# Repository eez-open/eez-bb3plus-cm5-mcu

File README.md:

### This is a WORK IN PROGRESS!

---

### Ownership and License
The contributors are listed in CONTRIB.TXT. 

Licenses | OSHWA UID
--|--
 | 

### Overview

The MCU module uses a high performance STM32 MCU and is pin compatible with Raspberry Pi CM5. The MCU cannot generate an HDMI compatible signal, so a [TI TFP410](https://www.ti.com/product/TFP410) is used to convert 24-bit RGB to HDMI compatible signal. Since the BB3+ offers dual display: a built-in 5" TFT touchscreen and an external monitor, a 1:2 high speed mux ([TS3DV642](https://www.ti.com/product/TS3DV642)) is used for destination selection.

### Feature list

* [Raspberry Pi CM5](https://www.raspberrypi.com/products/compute-module-5) form factor (55 x 45 mm)
* [STM32H7R7L8H6H](https://www.st.com/en/microcontrollers-microprocessors/stm32h7r7l8.html) 32-bit High-Performance Arm Cortex-M7 MCU, 600 MHz, NeoChrom GPU
* 32 MB PSRAM
* 32 MB Flash memory
* Micro SD Card socket
* Two USB ports (1x FS with [1:2 Mux](https://www.diodes.com/part/view/PI3USB102), 1x FS/HS)
* 10/100 Mbps Ethernet
* 24-bit color video output with 1:2 MUX (HDMI® compatible)
* 6-layer PCB (without buried/blind vias)

### Related topics and links

* Intergalaktik [BB3-CM4](https://intergalaktik.eu/projects/bb3-cm4)
* [EEZ BB3+](https://github.com/eez-open/eez-bb3plus)
* [DIB DCP405+](https://github.com/eez-open/dib-dcp405plus) power module
* [EEZ BB3](https://github.com/eez-open/modular-psu)
* [EEZ Studio](https://www.envox.eu/studio/studio-introduction)
* [Discord](https://discord.com/invite/q5KAeeenNG) server
* [X](https://x.com/envox) (ex Twitter)
* [YouTube](https://www.youtube.com/c/eezopen) channel
* [EEVblog forum](https://www.eevblog.com/forum/projects/eez-h25005-a-possible-successor-of-eez-h24005-programmable-power-supply/) discussion

---

This work is financed by [NLnet](https://nlnet.nl/project/BB3-CM5/) foundation

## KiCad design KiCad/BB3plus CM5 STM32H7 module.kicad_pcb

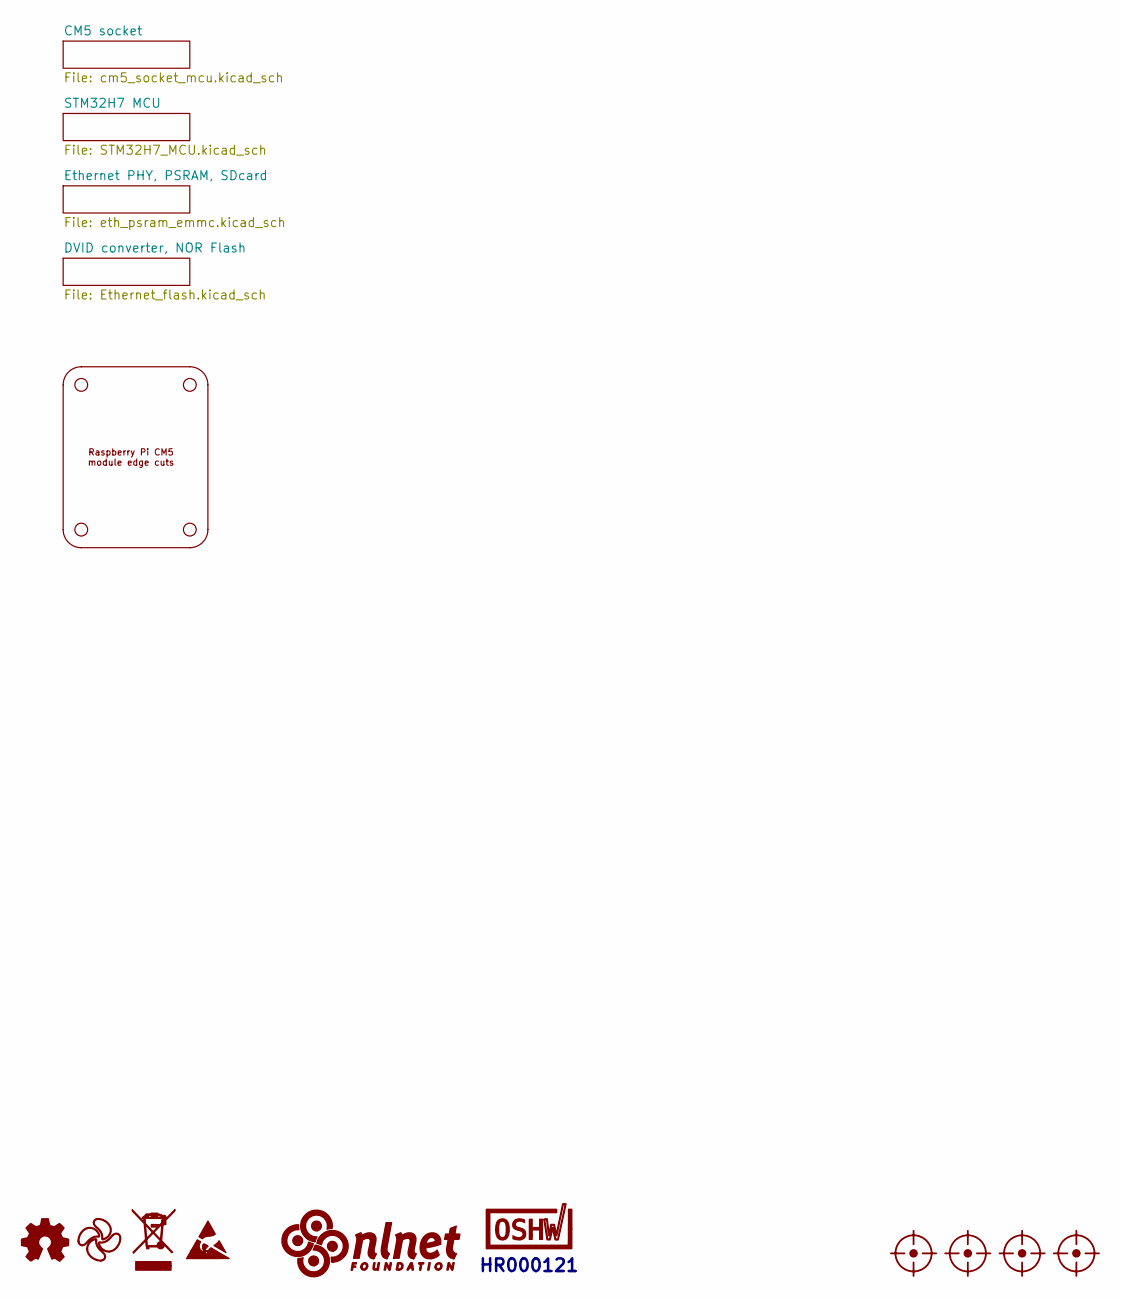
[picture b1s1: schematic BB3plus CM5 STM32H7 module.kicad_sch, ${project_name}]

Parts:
FM1, FM2, FM3, FM4: Fiducial_0.75mm_Mask1.5mm
LOGO1: Open HW logo; Open HW logo (5.7x6mm)
LOGO2: EEZ logo; EEZ logo (outline 6mm)
LOGO3: WEEE logo
LOGO4: ESD logo
LOGO5: NLnet logo
LOGO6: OSHWA logo; OSHWA logo 6.6mm
Module1: Raspberry-Pi-CM5 (SoM)_EdgeCuts

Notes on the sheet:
HR000121

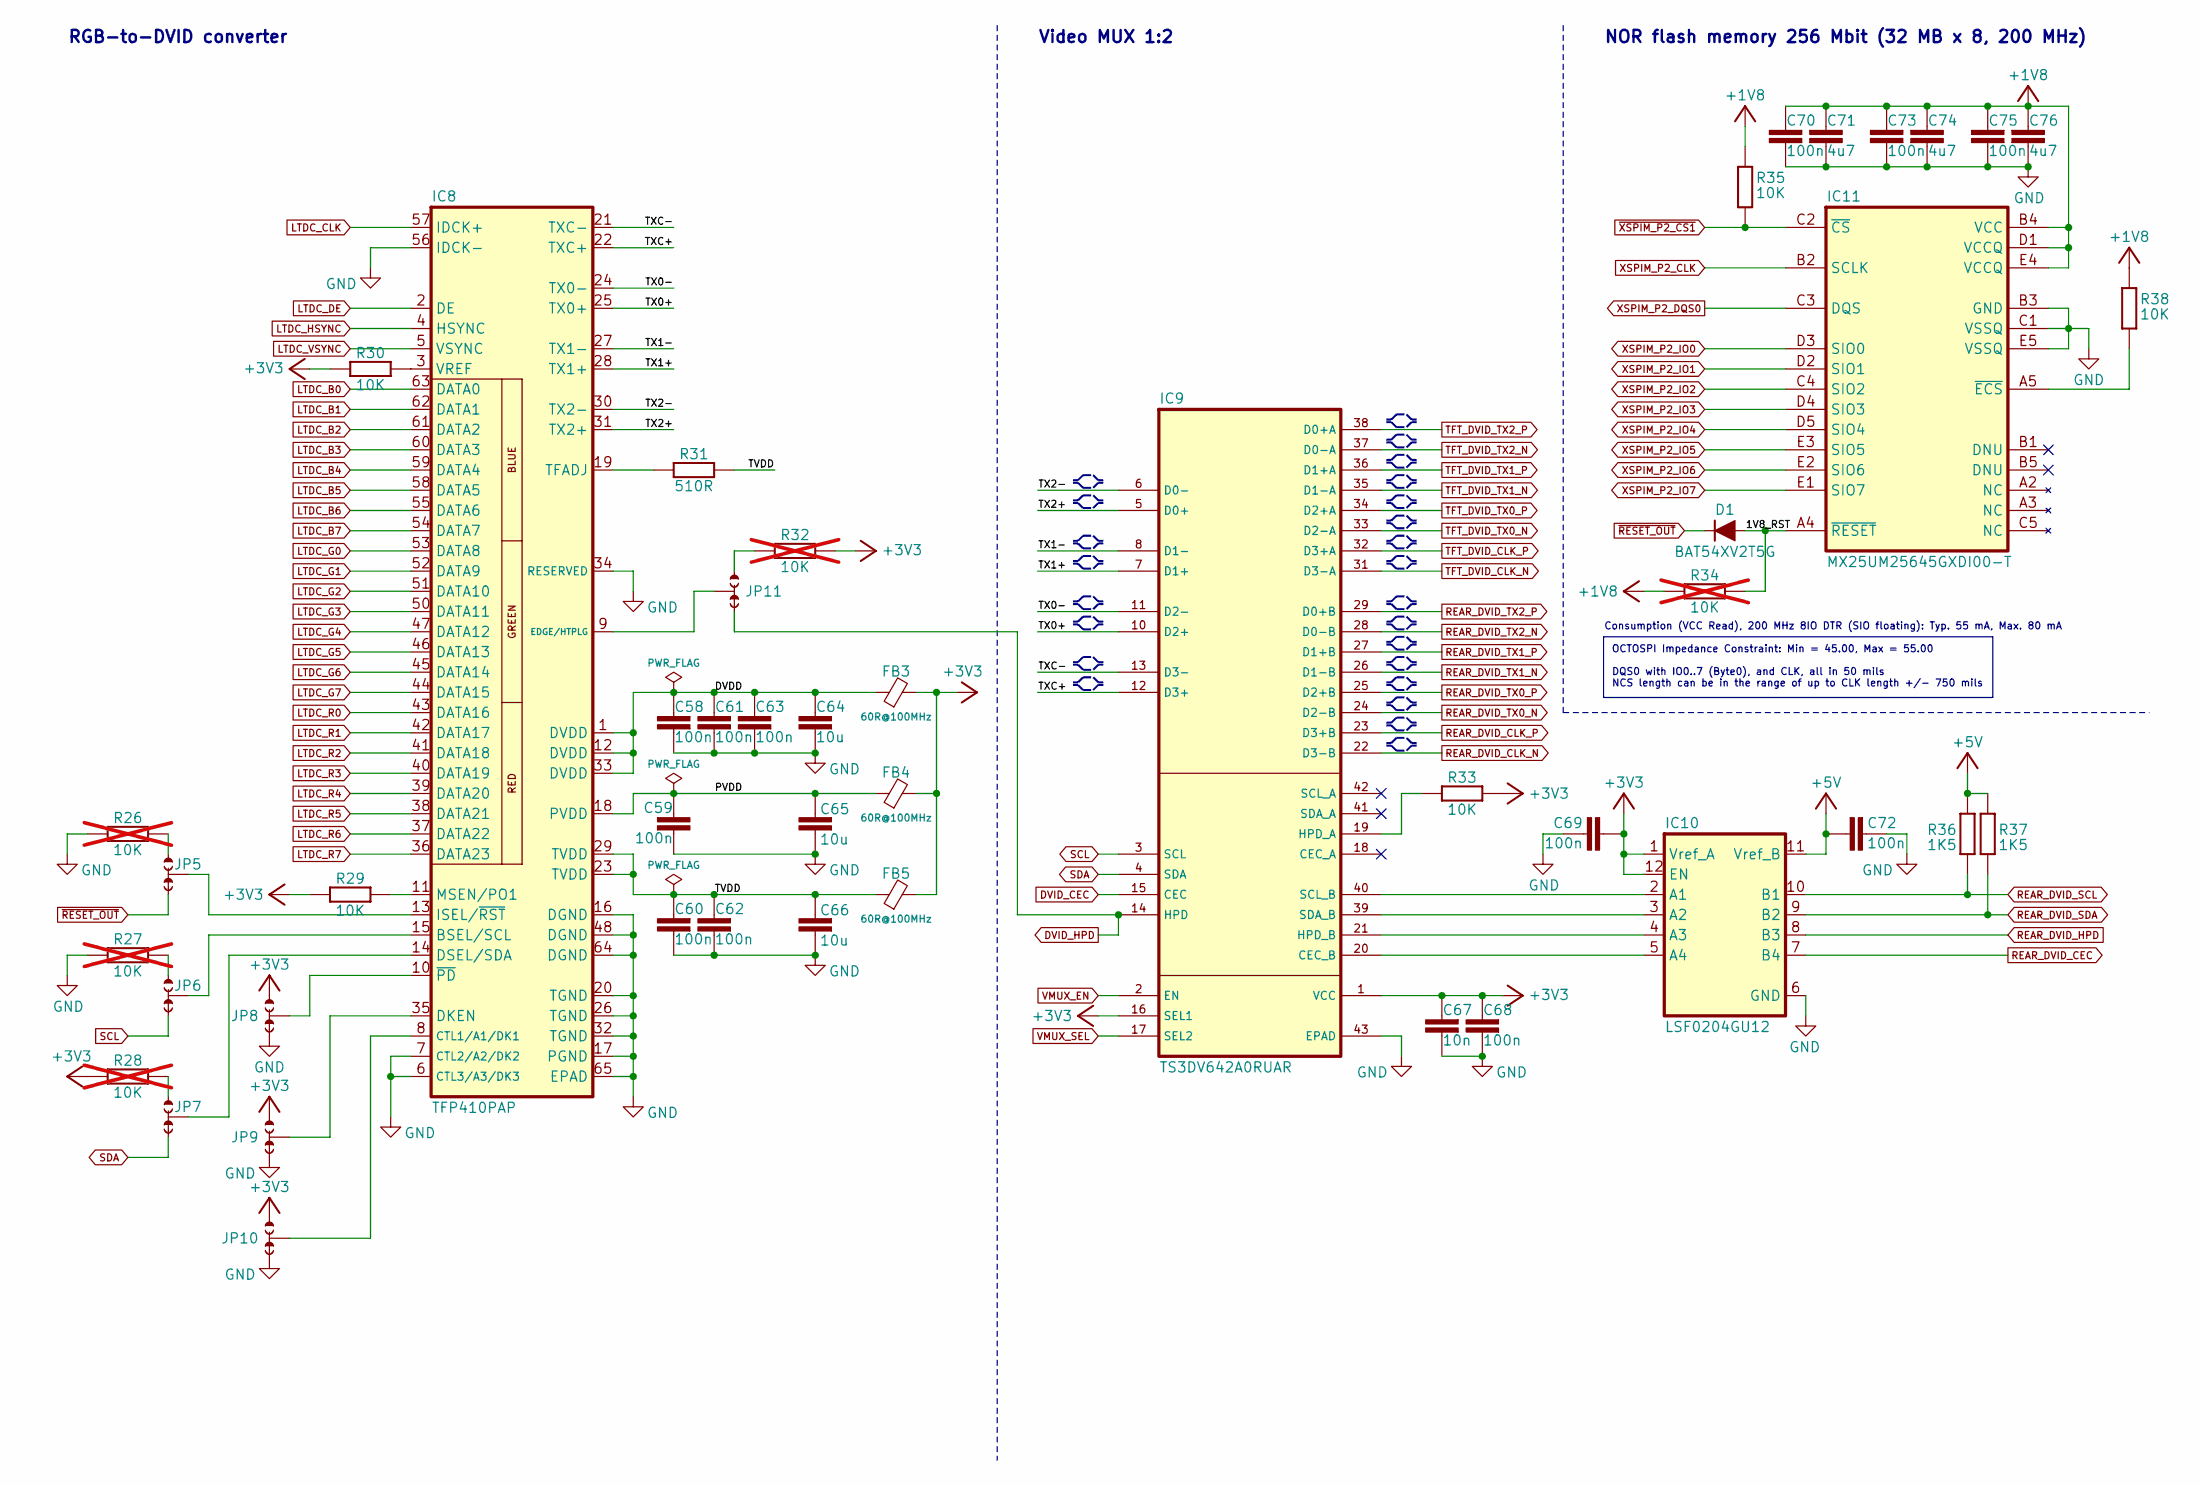
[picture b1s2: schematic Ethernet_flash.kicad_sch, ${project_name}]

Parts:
C58, C59, C60, C61, C62, C63, C68, C69, C70, C72, C73, C75: 100n; C_0402_1005Metric; DigiKey 490-6287-1-ND
C64, C65, C66: 10u; C_0603_1608Metric; DigiKey 1276-1052-6-ND
C67: 10n; C_0402_1005Metric; DigiKey 490-6309-1-ND
C71, C74, C76: 4u7; C_0603_1608Metric; DigiKey 1276-1044-1-ND
D1: BAT54XV2T5G; SOD-523F_0P9X1P3_ONS; DigiKey BAT54XV2T5GOSCT-ND
FB3, FB4, FB5: 60R@100MHz; BEAD0603; DigiKey 490-7809-1-ND
IC8: TFP410PAP; PAP64_5X5-L; DigiKey 296-12666-ND
IC9: TS3DV642A0RUAR; RUA42_7P55X2P05; DigiKey 296-39510-1-ND
IC10: LSF0204GU12; XQFN12_SOT1174-1_NEX-L; DigiKey 1727-LSF0204GU12-Q100XTR-ND
IC11: MX25UM25645GXDI00-T; APS256XXN-OBR-BG_APY-L; DigiKey 1092-MX25UM25645GXDI00-ND
JP5, JP6, JP7, JP8, JP9, JP10, JP11: JP3 shorted (0603)
R26, R27, R28, R32, R34: 10K; R_0402_1005Metric; DigiKey 311-10.0KLRCT-ND; not fitted
R29, R30, R33, R35, R38: 10K; R_0402_1005Metric; DigiKey 311-10.0KLRCT-ND
R31: 510R; R_0402_1005Metric; DigiKey 13-RC0402FR-13510RLCT-ND
R36, R37: 1K5; R_0402_1005Metric; DigiKey 311-1.50KLRCT-ND

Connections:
+1V8: C70.1, C71.1, C73.1, C74.1, C75.1, C76.1, IC11.B4 (VCC), IC11.D1 (VCCQ), IC11.E4 (VCCQ), R34.2, R35.2, R38.2; also elsewhere on the board
+3V3: C67.1, C68.1, C69.2, FB3.2, FB4.2, FB5.2, IC9.1 (VCC), IC9.16 (SEL1), IC10.1 (Vref_A), IC10.12 (EN), JP8.NO, JP9.NO, JP10.NO, R28.2, R29.1, R30.2, R32.2, R33.2; also elsewhere on the board
+5V: C72.2, IC10.11 (Vref_B), R36.2, R37.2; also elsewhere on the board
/DVID converter, NOR Flash/1V8_RST: D1.A, IC11.A4 (~RESET), R34.1
/DVID converter, NOR Flash/DVDD: C58.1, C61.1, C63.1, C64.1, FB3.1, IC8.1 (DVDD), IC8.12 (DVDD), IC8.33 (DVDD)
/DVID converter, NOR Flash/PVDD: C59.1, C65.2, FB4.1, IC8.18 (PVDD)
/DVID converter, NOR Flash/TVDD: C60.1, C62.1, C66.2, FB5.1, IC8.23 (TVDD), IC8.29 (TVDD), R31.2
/DVID converter, NOR Flash/TX0+: IC8.25 (TX0+), IC9.10 (D2+)
/DVID converter, NOR Flash/TX0-: IC8.24 (TX0-), IC9.11 (D2-)
/DVID converter, NOR Flash/TX1+: IC8.28 (TX1+), IC9.7 (D1+)
/DVID converter, NOR Flash/TX1-: IC8.27 (TX1-), IC9.8 (D1-)
/DVID converter, NOR Flash/TX2+: IC8.31 (TX2+), IC9.5 (D0+)
/DVID converter, NOR Flash/TX2-: IC8.30 (TX2-), IC9.6 (D0-)
/DVID converter, NOR Flash/TXC+: IC8.22 (TXC+), IC9.12 (D3+)
/DVID converter, NOR Flash/TXC-: IC8.21 (TXC-), IC9.13 (D3-)
DVID_CEC: IC9.15 (CEC); also elsewhere on the board
DVID_HPD: IC9.14 (HPD), JP11.NC; also elsewhere on the board
GND: C58.2, C59.2, C60.2, C61.2, C62.2, C63.2, C64.2, C65.1, C66.1, C67.2, C68.2, C69.1, C70.2, C71.2, C72.1, C73.2, C74.2, C75.2, C76.2, IC8.6 (CTL3/A3/DK3), IC8.7 (CTL2/A2/DK2), IC8.16 (DGND), IC8.17 (PGND), IC8.20 (TGND), IC8.26 (TGND), IC8.32 (TGND), IC8.34 (RESERVED), IC8.48 (DGND), IC8.56 (IDCK-), IC8.64 (DGND), IC8.65 (EPAD), IC9.43 (EPAD), IC10.6 (GND), IC11.B3 (GND), IC11.C1 (VSSQ), IC11.E5 (VSSQ), JP8.NC, JP9.NC, JP10.NC, R26.2, R27.2; also elsewhere on the board
LTDC_B0: IC8.63 (DATA0); also elsewhere on the board
LTDC_B1: IC8.62 (DATA1); also elsewhere on the board
LTDC_B2: IC8.61 (DATA2); also elsewhere on the board
LTDC_B3: IC8.60 (DATA3); also elsewhere on the board
LTDC_B4: IC8.59 (DATA4); also elsewhere on the board
LTDC_B5: IC8.58 (DATA5); also elsewhere on the board
LTDC_B6: IC8.55 (DATA6); also elsewhere on the board
LTDC_B7: IC8.54 (DATA7); also elsewhere on the board
LTDC_CLK: IC8.57 (IDCK+); also elsewhere on the board
LTDC_DE: IC8.2 (DE); also elsewhere on the board
LTDC_G0: IC8.53 (DATA8); also elsewhere on the board
LTDC_G1: IC8.52 (DATA9); also elsewhere on the board
LTDC_G2: IC8.51 (DATA10); also elsewhere on the board
LTDC_G3: IC8.50 (DATA11); also elsewhere on the board
LTDC_G4: IC8.47 (DATA12); also elsewhere on the board
LTDC_G5: IC8.46 (DATA13); also elsewhere on the board
LTDC_G6: IC8.45 (DATA14); also elsewhere on the board
LTDC_G7: IC8.44 (DATA15); also elsewhere on the board
LTDC_HSYNC: IC8.4 (HSYNC); also elsewhere on the board
LTDC_R0: IC8.43 (DATA16); also elsewhere on the board
LTDC_R1: IC8.42 (DATA17); also elsewhere on the board
LTDC_R2: IC8.41 (DATA18); also elsewhere on the board
LTDC_R3: IC8.40 (DATA19); also elsewhere on the board
LTDC_R4: IC8.39 (DATA20); also elsewhere on the board
LTDC_R5: IC8.38 (DATA21); also elsewhere on the board
LTDC_R6: IC8.37 (DATA22); also elsewhere on the board
LTDC_R7: IC8.36 (DATA23); also elsewhere on the board
LTDC_VSYNC: IC8.5 (VSYNC); also elsewhere on the board
unnamed: IC8.15 (BSEL/SCL), JP6.COM
unnamed: IC8.8 (CTL1/A1/DK1), JP10.COM
unnamed: IC8.35 (DKEN), JP9.COM
unnamed: IC8.14 (DSEL/SDA), JP7.COM
unnamed: IC8.9 (EDGE/HTPLG), JP11.COM
unnamed: IC8.13 (ISEL/~RST), JP5.COM
unnamed: IC8.11 (MSEN/PO1), R29.2
unnamed: IC8.19 (TFADJ), R31.1
unnamed: IC8.3 (VREF), R30.1
unnamed: IC8.10 (~PD), JP8.COM
unnamed: IC9.19 (HPD_A), R33.1
unnamed: IC9.40 (SCL_B), IC10.2 (A1)
unnamed: IC9.39 (SDA_B), IC10.3 (A2)
unnamed: IC9.21 (HPD_B), IC10.4 (A3)
unnamed: IC9.20 (CEC_B), IC10.5 (A4)
unnamed: IC11.A5 (~ECS), R38.1
unnamed: JP5.NO, R26.1
unnamed: JP6.NO, R27.1
unnamed: JP7.NO, R28.1
unnamed: JP11.NO, R32.1
REAR_DVID_CEC: IC10.7 (B4); also elsewhere on the board
REAR_DVID_CLK_N: IC9.22 (D3-B); also elsewhere on the board
REAR_DVID_CLK_P: IC9.23 (D3+B); also elsewhere on the board
REAR_DVID_HPD: IC10.8 (B3); also elsewhere on the board
REAR_DVID_SCL: IC10.10 (B1), R36.1; also elsewhere on the board
REAR_DVID_SDA: IC10.9 (B2), R37.1; also elsewhere on the board
REAR_DVID_TX0_N: IC9.24 (D2-B); also elsewhere on the board
REAR_DVID_TX0_P: IC9.25 (D2+B); also elsewhere on the board
REAR_DVID_TX1_N: IC9.26 (D1-B); also elsewhere on the board
REAR_DVID_TX1_P: IC9.27 (D1+B); also elsewhere on the board
REAR_DVID_TX2_N: IC9.28 (D0-B); also elsewhere on the board
REAR_DVID_TX2_P: IC9.29 (D0+B); also elsewhere on the board
SCL: IC9.3 (SCL), JP6.NC; also elsewhere on the board
SDA: IC9.4 (SDA), JP7.NC; also elsewhere on the board
TFT_DVID_CLK_N: IC9.31 (D3-A); also elsewhere on the board
TFT_DVID_CLK_P: IC9.32 (D3+A); also elsewhere on the board
TFT_DVID_TX0_N: IC9.33 (D2-A); also elsewhere on the board
TFT_DVID_TX0_P: IC9.34 (D2+A); also elsewhere on the board
TFT_DVID_TX1_N: IC9.35 (D1-A); also elsewhere on the board
TFT_DVID_TX1_P: IC9.36 (D1+A); also elsewhere on the board
TFT_DVID_TX2_N: IC9.37 (D0-A); also elsewhere on the board
TFT_DVID_TX2_P: IC9.38 (D0+A); also elsewhere on the board
VMUX_EN: IC9.2 (EN); also elsewhere on the board
VMUX_SEL: IC9.17 (SEL2); also elsewhere on the board
XSPIM_P2_CLK: IC11.B2 (SCLK); also elsewhere on the board
XSPIM_P2_DQS0: IC11.C3 (DQS); also elsewhere on the board
XSPIM_P2_IO0: IC11.D3 (SIO0); also elsewhere on the board
XSPIM_P2_IO1: IC11.D2 (SIO1); also elsewhere on the board
XSPIM_P2_IO2: IC11.C4 (SIO2); also elsewhere on the board
XSPIM_P2_IO3: IC11.D4 (SIO3); also elsewhere on the board
XSPIM_P2_IO4: IC11.D5 (SIO4); also elsewhere on the board
XSPIM_P2_IO5: IC11.E3 (SIO5); also elsewhere on the board
XSPIM_P2_IO6: IC11.E2 (SIO6); also elsewhere on the board
XSPIM_P2_IO7: IC11.E1 (SIO7); also elsewhere on the board
~RESET_OUT: D1.C, JP5.NC; also elsewhere on the board
~XSPIM_P2_CS1: IC11.C2 (~CS), R35.1; also elsewhere on the board

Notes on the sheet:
RGB-to-DVID converter
Video MUX 1:2
Consumption (VCC Read), 200 MHz 8IO DTR (SIO floating): Typ. 55 mA, Max. 80 mA
NOR flash memory 256 Mbit (32 MB x 8, 200 MHz)
OCTOSPI Impedance Constraint: Min = 45.00, Max = 55.00 DQS0 with IO0..7 (Byte0), and CLK, all in 50 mils NCS length can be in the range of up to CLK length +/- 750 mils

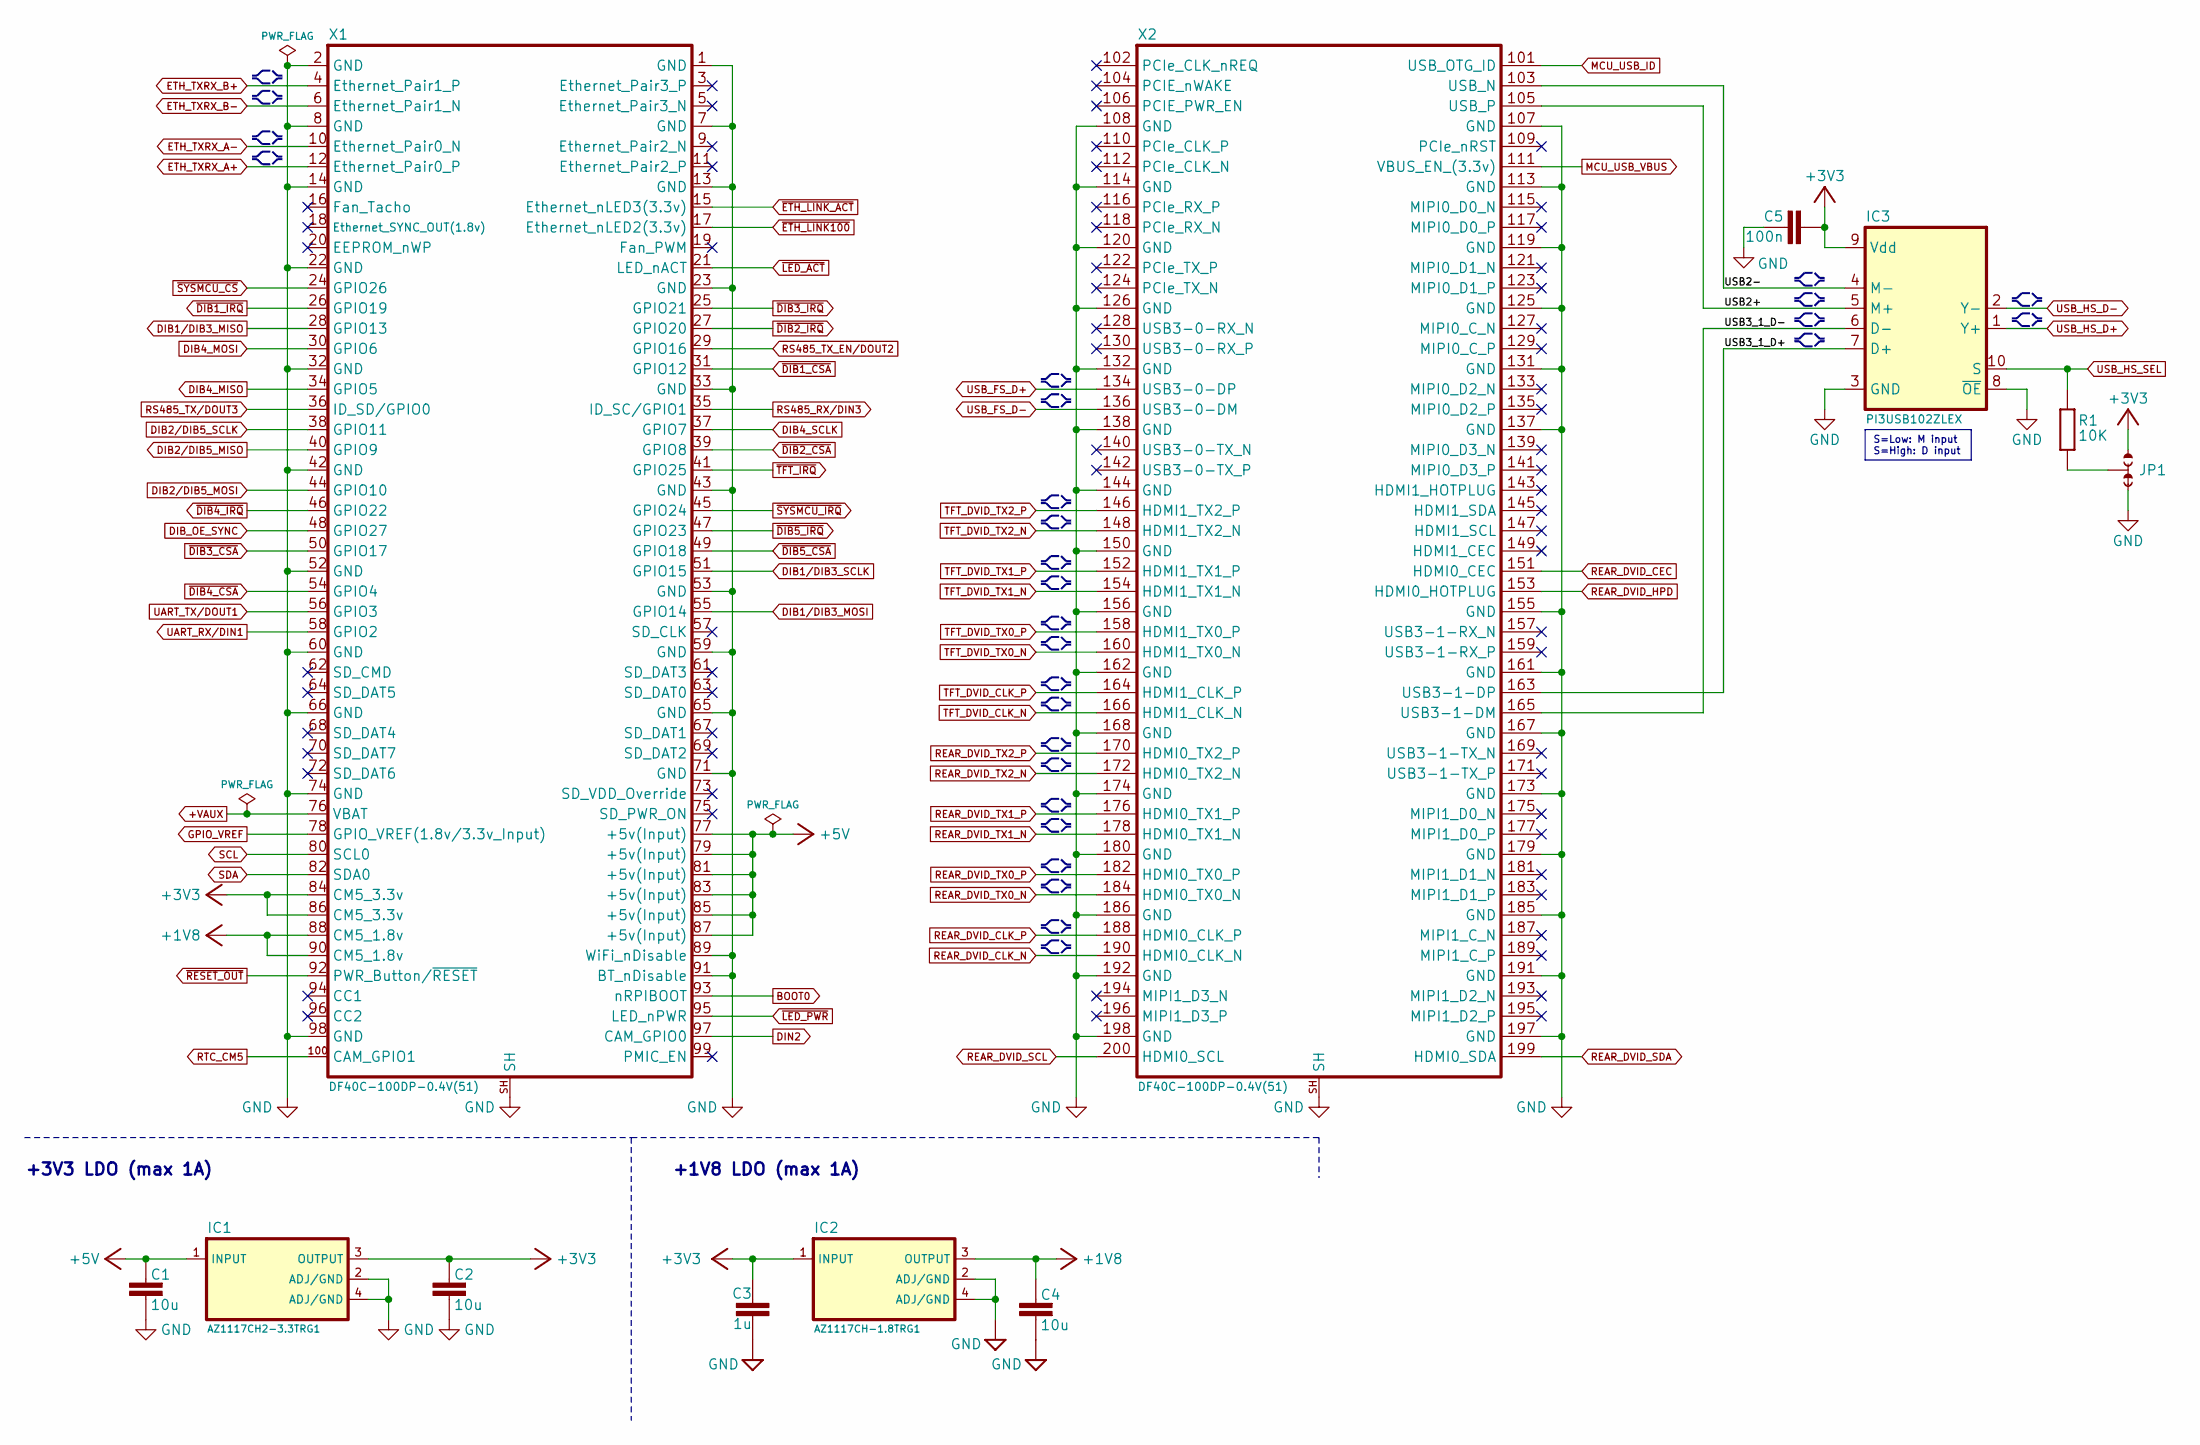
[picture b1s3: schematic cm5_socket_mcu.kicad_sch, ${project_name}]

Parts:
C1, C2, C4: 10u; C_0603_1608Metric; DigiKey 1276-1052-6-ND
C3: 1u; C_0402_1005Metric; DigiKey 490-GRM155C81A105MA12DCT-ND
C5: 100n; C_0402_1005Metric; DigiKey 490-6287-1-ND
IC1: AZ1117CH2-3.3TRG1; SOT223; DigiKey 31-AZ1117CH2-3.3TRG1CT-ND
IC2: AZ1117CH-1.8TRG1; SOT223; DigiKey AZ1117CH-1.8TRG1DICT-ND
IC3: PI3USB102ZLEX; TQFN-10; DigiKey PI3USB102ZLEXCT-ND
JP1: JP3 shorted (0603)
R1: 10K; R_0402_1005Metric; DigiKey 311-10.0KLRCT-ND
X1: DF40C-100DP-0.4V(51); Raspberry-Pi-CM5 (SoM)_Left; DigiKey H11614CT-ND
X2: DF40C-100DP-0.4V(51); Raspberry-Pi-CM5 (SoM)_Right; DigiKey H11614CT-ND

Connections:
+1V8: C4.2, IC2.3 (OUTPUT), X1.88 (CM5_1.8v), X1.90 (CM5_1.8v); also elsewhere on the board
+3V3: C2.2, C3.1, C5.2, IC1.3 (OUTPUT), IC2.1 (INPUT), IC3.9 (Vdd), JP1.NO, X1.84 (CM5_3.3v), X1.86 (CM5_3.3v); also elsewhere on the board
+5V: C1.2, IC1.1 (INPUT), X1.77 (+5v(Input)), X1.79 (+5v(Input)), X1.81 (+5v(Input)), X1.83 (+5v(Input)), X1.85 (+5v(Input)), X1.87 (+5v(Input)); also elsewhere on the board
+VAUX: X1.76 (VBAT); also elsewhere on the board
/CM5 socket/USB2+: IC3.5 (M+), X2.105 (USB_P)
/CM5 socket/USB2-: IC3.4 (M-), X2.103 (USB_N)
/CM5 socket/USB3_1_D+: IC3.7 (D+), X2.163 (USB3-1-DP)
/CM5 socket/USB3_1_D-: IC3.6 (D-), X2.165 (USB3-1-DM)
BOOT0: X1.93 (nRPIBOOT); also elsewhere on the board
DIB1/DIB3_MISO: X1.28 (GPIO13); also elsewhere on the board
DIB1/DIB3_MOSI: X1.55 (GPIO14); also elsewhere on the board
DIB1/DIB3_SCLK: X1.51 (GPIO15); also elsewhere on the board
DIB2/DIB5_MISO: X1.40 (GPIO9); also elsewhere on the board
DIB2/DIB5_MOSI: X1.44 (GPIO10); also elsewhere on the board
DIB2/DIB5_SCLK: X1.38 (GPIO11); also elsewhere on the board
DIB4_MISO: X1.34 (GPIO5); also elsewhere on the board
DIB4_MOSI: X1.30 (GPIO6); also elsewhere on the board
DIB4_SCLK: X1.37 (GPIO7); also elsewhere on the board
DIB_OE_SYNC: X1.48 (GPIO27); also elsewhere on the board
DIN2: X1.97 (CAM_GPIO0); also elsewhere on the board
ETH_TXRX_A+: X1.12 (Ethernet_Pair0_P); also elsewhere on the board
ETH_TXRX_A-: X1.10 (Ethernet_Pair0_N); also elsewhere on the board
ETH_TXRX_B+: X1.4 (Ethernet_Pair1_P); also elsewhere on the board
ETH_TXRX_B-: X1.6 (Ethernet_Pair1_N); also elsewhere on the board
GND: C1.1, C2.1, C3.2, C4.1, C5.1, IC1.2 (ADJ/GND), IC1.4 (ADJ/GND), IC2.2 (ADJ/GND), IC2.4 (ADJ/GND), IC3.3 (GND), IC3.8 (~OE), JP1.NC, X1.1 (GND), X1.2 (GND), X1.7 (GND), X1.8 (GND), X1.13 (GND), X1.14 (GND), X1.22 (GND), X1.23 (GND), X1.32 (GND), X1.33 (GND), X1.42 (GND), X1.43 (GND), X1.52 (GND), X1.53 (GND), X1.59 (GND), X1.60 (GND), X1.65 (GND), X1.66 (GND), X1.71 (GND), X1.74 (GND), X1.89 (WiFi_nDisable), X1.91 (BT_nDisable), X1.98 (GND), X1.SH, X2.107 (GND), X2.108 (GND), X2.113 (GND), X2.114 (GND), X2.119 (GND), X2.120 (GND), X2.125 (GND), X2.126 (GND), X2.131 (GND), X2.132 (GND), X2.137 (GND), X2.138 (GND), X2.144 (GND), X2.150 (GND), X2.155 (GND), X2.156 (GND), X2.161 (GND), X2.162 (GND), X2.167 (GND), X2.168 (GND), X2.173 (GND), X2.174 (GND), X2.179 (GND), X2.180 (GND), X2.185 (GND), X2.186 (GND), X2.191 (GND), X2.192 (GND), X2.197 (GND), X2.198 (GND), X2.SH; also elsewhere on the board
GPIO_VREF: X1.78 (GPIO_VREF(1.8v/3.3v_Input)); also elsewhere on the board
MCU_USB_ID: X2.101 (USB_OTG_ID); also elsewhere on the board
MCU_USB_VBUS: X2.111 (VBUS_EN_(3.3v)); also elsewhere on the board
unnamed: JP1.COM, R1.1
REAR_DVID_CEC: X2.151 (HDMI0_CEC); also elsewhere on the board
REAR_DVID_CLK_N: X2.190 (HDMI0_CLK_N); also elsewhere on the board
REAR_DVID_CLK_P: X2.188 (HDMI0_CLK_P); also elsewhere on the board
REAR_DVID_HPD: X2.153 (HDMI0_HOTPLUG); also elsewhere on the board
REAR_DVID_SCL: X2.200 (HDMI0_SCL); also elsewhere on the board
REAR_DVID_SDA: X2.199 (HDMI0_SDA); also elsewhere on the board
REAR_DVID_TX0_N: X2.184 (HDMI0_TX0_N); also elsewhere on the board
REAR_DVID_TX0_P: X2.182 (HDMI0_TX0_P); also elsewhere on the board
REAR_DVID_TX1_N: X2.178 (HDMI0_TX1_N); also elsewhere on the board
REAR_DVID_TX1_P: X2.176 (HDMI0_TX1_P); also elsewhere on the board
REAR_DVID_TX2_N: X2.172 (HDMI0_TX2_N); also elsewhere on the board
REAR_DVID_TX2_P: X2.170 (HDMI0_TX2_P); also elsewhere on the board
RS485_RX/DIN3: X1.35 (ID_SC/GPIO1); also elsewhere on the board
RS485_TX_EN/DOUT2: X1.29 (GPIO16); also elsewhere on the board
RS485_TX/DOUT3: X1.36 (ID_SD/GPIO0); also elsewhere on the board
RTC_CM5: X1.100 (CAM_GPIO1); also elsewhere on the board
SCL: X1.80 (SCL0); also elsewhere on the board
SDA: X1.82 (SDA0); also elsewhere on the board
TFT_DVID_CLK_N: X2.166 (HDMI1_CLK_N); also elsewhere on the board
TFT_DVID_CLK_P: X2.164 (HDMI1_CLK_P); also elsewhere on the board
TFT_DVID_TX0_N: X2.160 (HDMI1_TX0_N); also elsewhere on the board
TFT_DVID_TX0_P: X2.158 (HDMI1_TX0_P); also elsewhere on the board
TFT_DVID_TX1_N: X2.154 (HDMI1_TX1_N); also elsewhere on the board
TFT_DVID_TX1_P: X2.152 (HDMI1_TX1_P); also elsewhere on the board
TFT_DVID_TX2_N: X2.148 (HDMI1_TX2_N); also elsewhere on the board
TFT_DVID_TX2_P: X2.146 (HDMI1_TX2_P); also elsewhere on the board
UART_RX/DIN1: X1.58 (GPIO2); also elsewhere on the board
UART_TX/DOUT1: X1.56 (GPIO3); also elsewhere on the board
USB_FS_D+: X2.134 (USB3-0-DP); also elsewhere on the board
USB_FS_D-: X2.136 (USB3-0-DM); also elsewhere on the board
USB_HS_D+: IC3.1 (Y+); also elsewhere on the board
USB_HS_D-: IC3.2 (Y-); also elsewhere on the board
USB_HS_SEL: IC3.10 (S), R1.2; also elsewhere on the board
~DIB1_CSA: X1.31 (GPIO12); also elsewhere on the board
~DIB1_IRQ: X1.26 (GPIO19); also elsewhere on the board
~DIB2_CSA: X1.39 (GPIO8); also elsewhere on the board
~DIB2_IRQ: X1.27 (GPIO20); also elsewhere on the board
~DIB3_CSA: X1.50 (GPIO17); also elsewhere on the board
~DIB3_IRQ: X1.25 (GPIO21); also elsewhere on the board
~DIB4_CSA: X1.54 (GPIO4); also elsewhere on the board
~DIB4_IRQ: X1.46 (GPIO22); also elsewhere on the board
~DIB5_CSA: X1.49 (GPIO18); also elsewhere on the board
~DIB5_IRQ: X1.47 (GPIO23); also elsewhere on the board
~ETH_LINK100: X1.17 (Ethernet_nLED2(3.3v)); also elsewhere on the board
~ETH_LINK_ACT: X1.15 (Ethernet_nLED3(3.3v)); also elsewhere on the board
~LED_ACT: X1.21 (LED_nACT); also elsewhere on the board
~LED_PWR: X1.95 (LED_nPWR); also elsewhere on the board
~RESET_OUT: X1.92 (PWR_Button/~RESET); also elsewhere on the board
~SYSMCU_CS: X1.24 (GPIO26); also elsewhere on the board
~SYSMCU_IRQ: X1.45 (GPIO24); also elsewhere on the board
~TFT_IRQ: X1.41 (GPIO25); also elsewhere on the board

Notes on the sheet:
+1V8 LDO (max 1A)
+3V3 LDO (max 1A)
S=Low: M input S=High: D input

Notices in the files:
parts and their libraries:
project_license: Licensed under the TAPR Open Hardware License (www.tapr.org/OHL)
